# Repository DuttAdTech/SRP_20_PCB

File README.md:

### Changes Suggested by Team
- Add Debug Headers for UART Lines for GSM.
- LORA Module Footprint adjust for Hand Soldering.
- Check SRAM Compatibility - 2 MBit.
- Add Resettable Fuse after SM712 Protection Diode on MB Lines.
- Display connector change in PCB.
- PCB partision layer change (edge cut).
- Make LDO based power supply.
- SDA SCL of ADS1115 need to connected properly.
- Vbat pin of the battery measurement need to connected to the MCU.
- Add 100uF capacitor(x2) in GSM.
- Logic level shifter footprint should be SC70.
- Ground of the optocoupler and Trip should be different
- Voltage for the TFT display should be checked before doing PCB connections.

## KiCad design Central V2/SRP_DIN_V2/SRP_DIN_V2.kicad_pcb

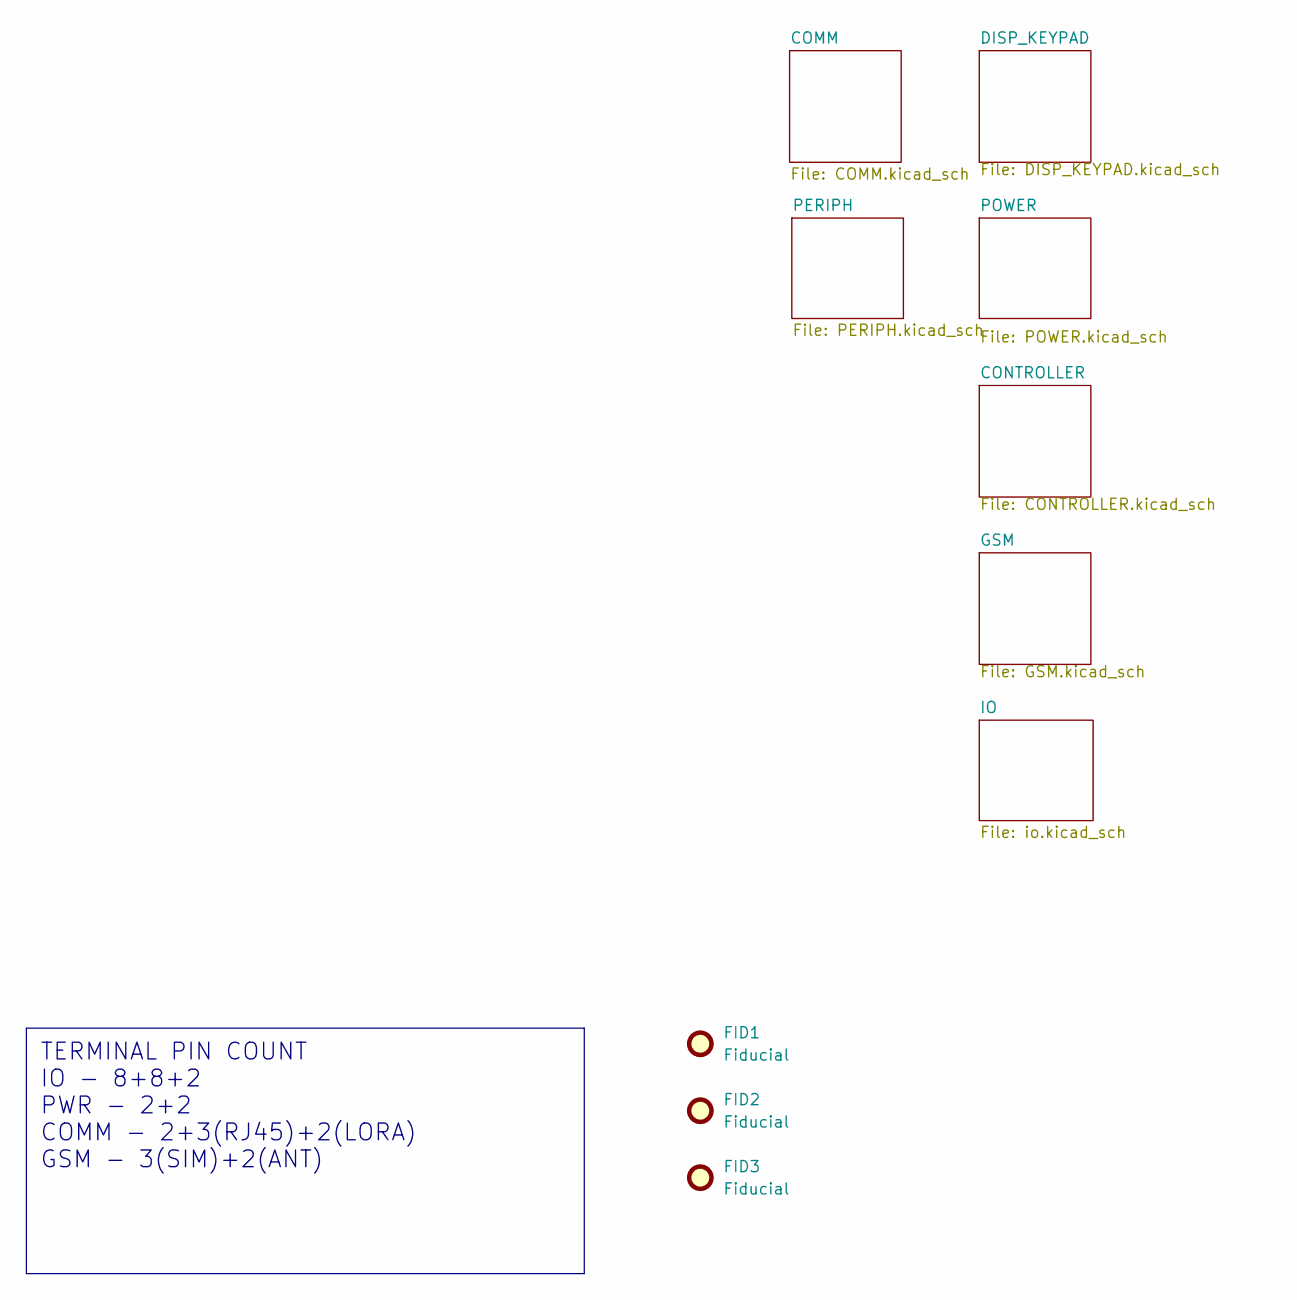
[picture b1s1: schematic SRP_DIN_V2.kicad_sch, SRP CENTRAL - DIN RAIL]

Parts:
FID1, FID2, FID3: Fiducial; Fiducial_1mm_Mask2mm

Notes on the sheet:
TERMINAL PIN COUNT IO - 8+8+2 PWR - 2+2 COMM - 2+3(RJ45)+2(LORA) GSM - 3(SIM)+2(ANT)

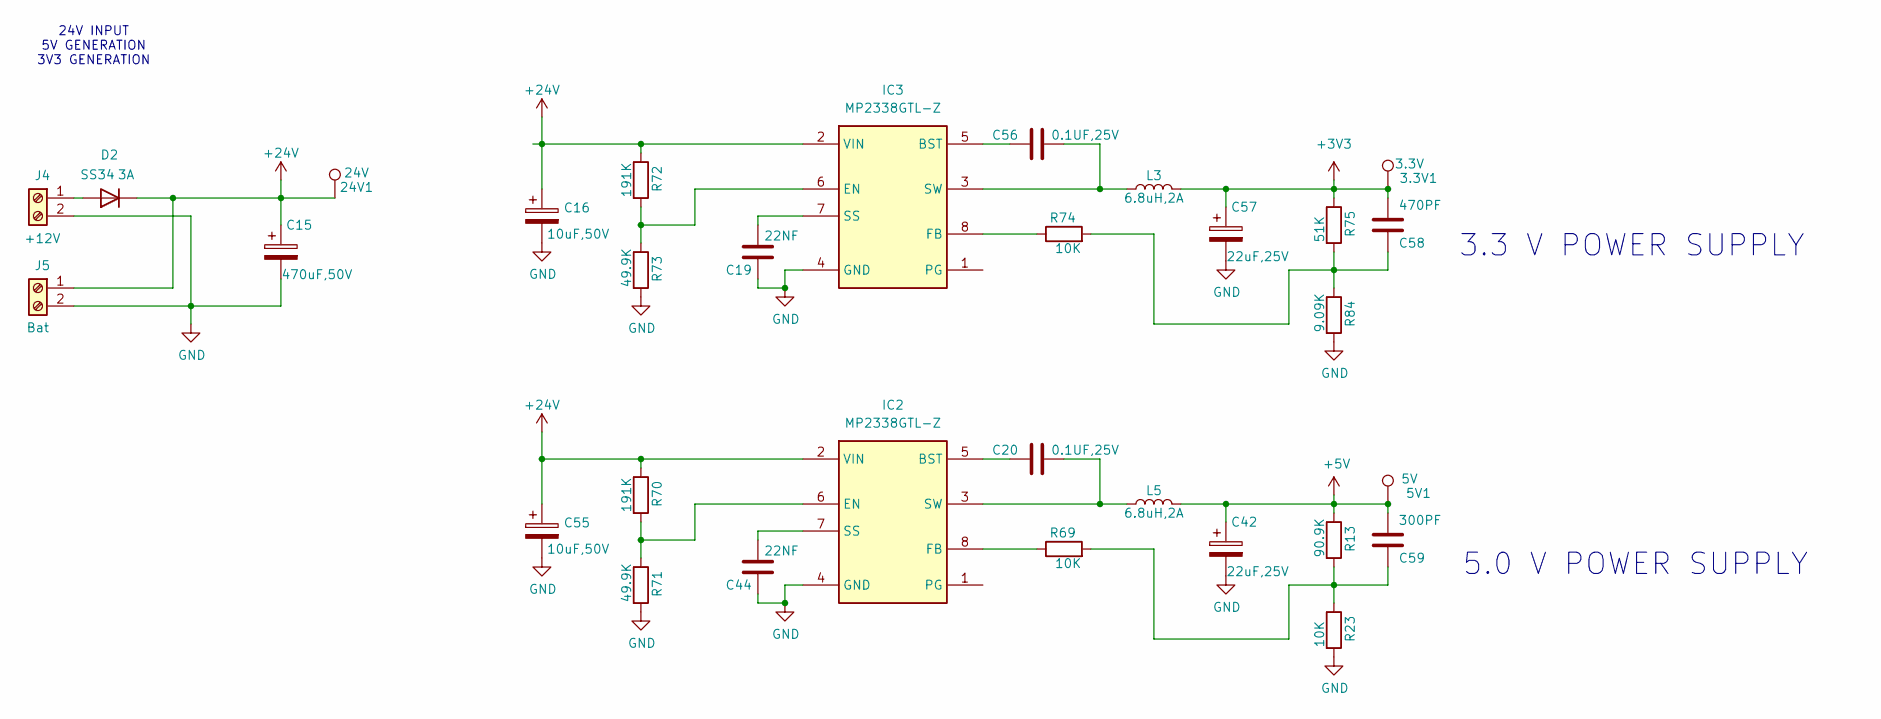
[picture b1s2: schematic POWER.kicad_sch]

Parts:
3.3V1: 3.3V; TestPoint_Pad_1.0x1.0mm
5V1: 5V; TestPoint_Pad_1.0x1.0mm
24V1: 24V; TestPoint_Pad_1.0x1.0mm
C15: 470uF,50V; CP_Elec_10x10.5
C16, C55: 10uF,50V; CP_Elec_8x5.4
C19, C44: 22NF; C_0805_2012Metric
C20, C56: 0.1UF,25V; C_0805_2012Metric
C42, C57: 22uF,25V; CP_Elec_6.3x5.3
C58: 470PF; C_0805_2012Metric
C59: 300PF; C_0805_2012Metric
D2: SS34; D_SMA
IC2, IC3: MP2338GTL-Z; SOT-583-8; Mouser Part Number 946-MP2338GTL-Z
J4: +12V; TerminalBlock_Phoenix_MKDS-3-2-5.08_1x02_P5.08mm_Horizontal
J5: Bat; TerminalBlock_Phoenix_MKDS-3-2-5.08_1x02_P5.08mm_Horizontal
L3, L5: 6.8uH,2A; L_2010_5025Metric
R13: 90.9K; R_0805_2012Metric_Pad1.20x1.40mm_HandSolder
R23, R69, R74: 10K; R_0805_2012Metric_Pad1.20x1.40mm_HandSolder
R70, R72: 191K; R_0805_2012Metric_Pad1.20x1.40mm_HandSolder
R71, R73: 49.9K; R_0805_2012Metric_Pad1.20x1.40mm_HandSolder
R75: 51K; R_0805_2012Metric_Pad1.20x1.40mm_HandSolder
R84: 9.09K; R_0805_2012Metric_Pad1.20x1.40mm_HandSolder

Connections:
+3V3: 3.3V1.1, C57.1, C58.2, L3.2, R75.1; also elsewhere on the board
+5V: 5V1.1, C42.1, C59.2, L5.2, R13.1; also elsewhere on the board
+24V: 24V1.1, C15.1, C16.1, C55.1, D2.1 (K), IC2.2 (VIN), IC3.2 (VIN), J5.1, R70.1, R72.1; also elsewhere on the board
GND: C15.2, C16.2, C19.1, C42.2, C44.1, C55.2, C57.2, IC2.4 (GND), IC3.4 (GND), J4.2, J5.2, R23.2, R71.2, R73.2, R84.2; also elsewhere on the board
unnamed: C58.1, R74.2, R75.2, R84.1
unnamed: C59.1, R13.2, R23.1, R69.2
unnamed: D2.2 (A), J4.1
unnamed: C20.1, IC2.5 (BST)
unnamed: IC2.6 (EN), R70.2, R71.1
unnamed: IC2.8 (FB), R69.1
unnamed: C44.2, IC2.7 (SS)
unnamed: C20.2, IC2.3 (SW), L5.1
unnamed: C56.1, IC3.5 (BST)
unnamed: IC3.6 (EN), R72.2, R73.1
unnamed: IC3.8 (FB), R74.1
unnamed: C19.2, IC3.7 (SS)
unnamed: C56.2, IC3.3 (SW), L3.1

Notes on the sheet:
3.3 V POWER SUPPLY
5.0 V POWER SUPPLY
24V INPUT 5V GENERATION 3V3 GENERATION

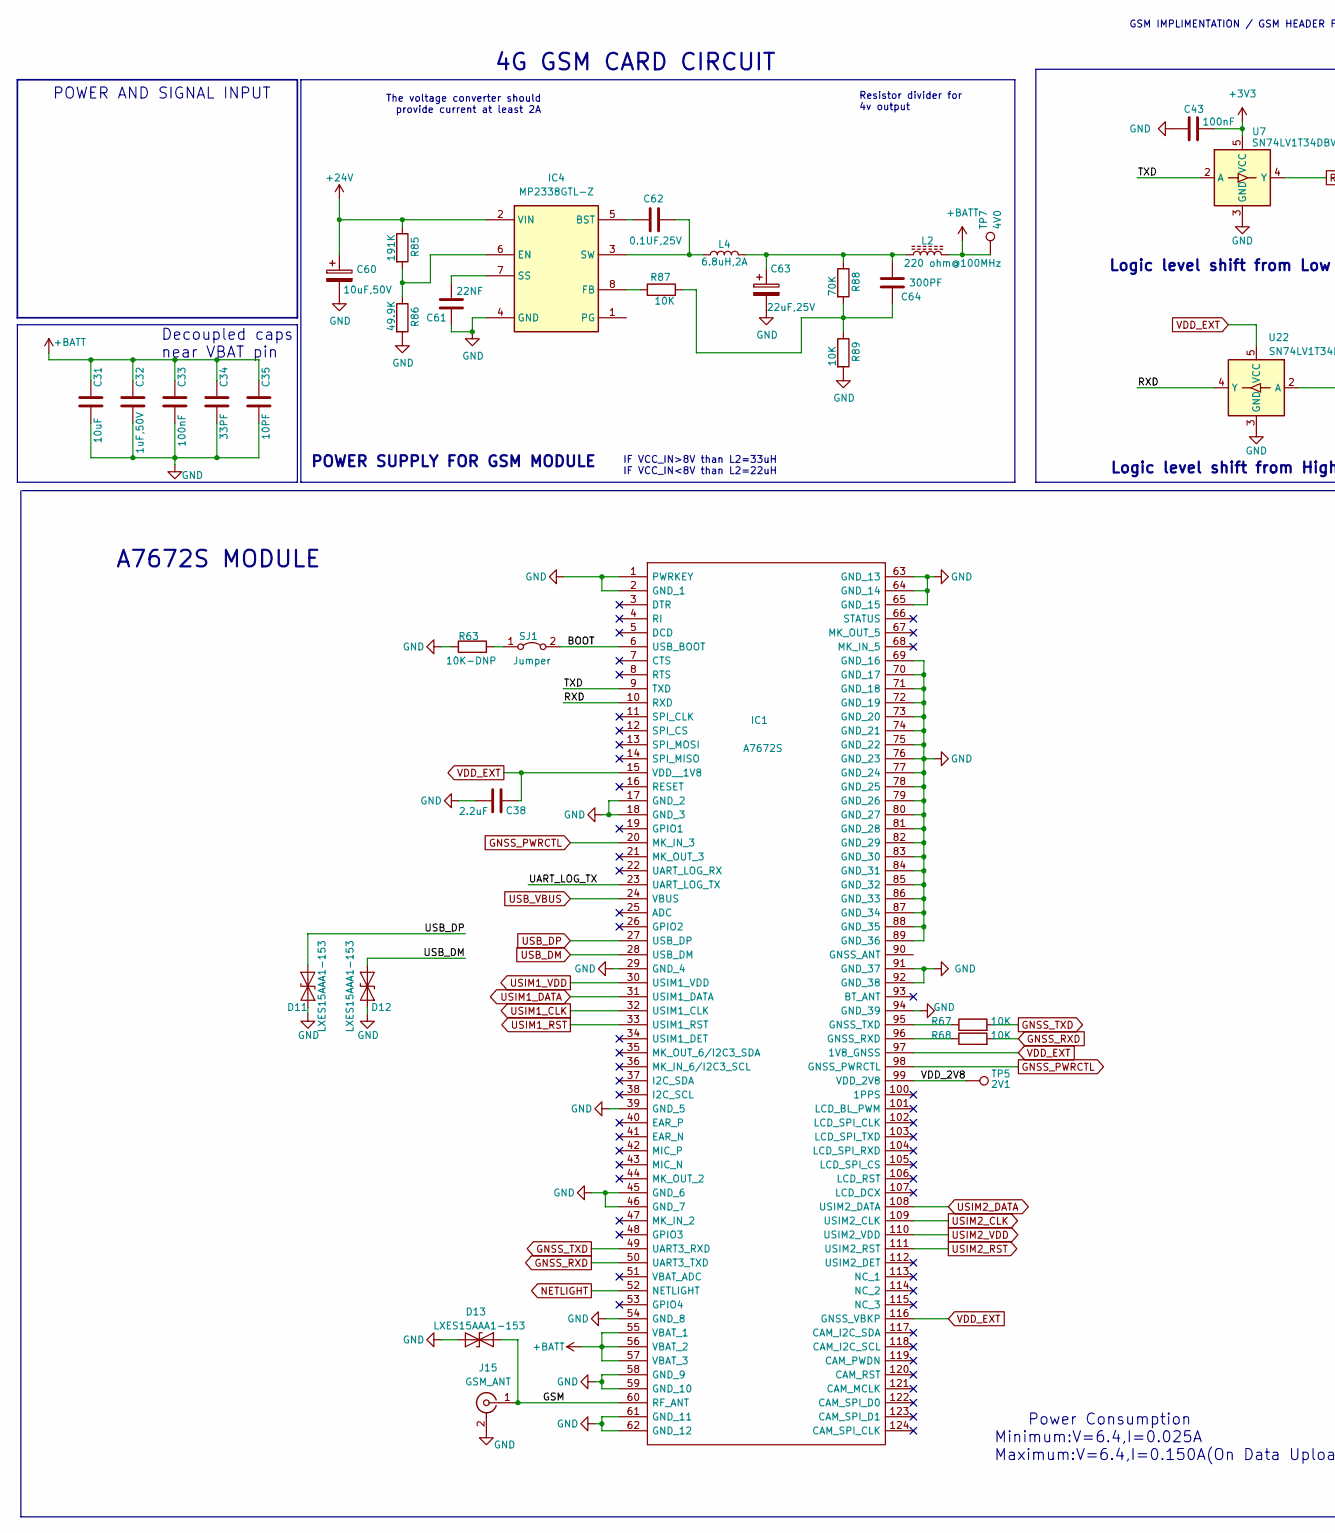
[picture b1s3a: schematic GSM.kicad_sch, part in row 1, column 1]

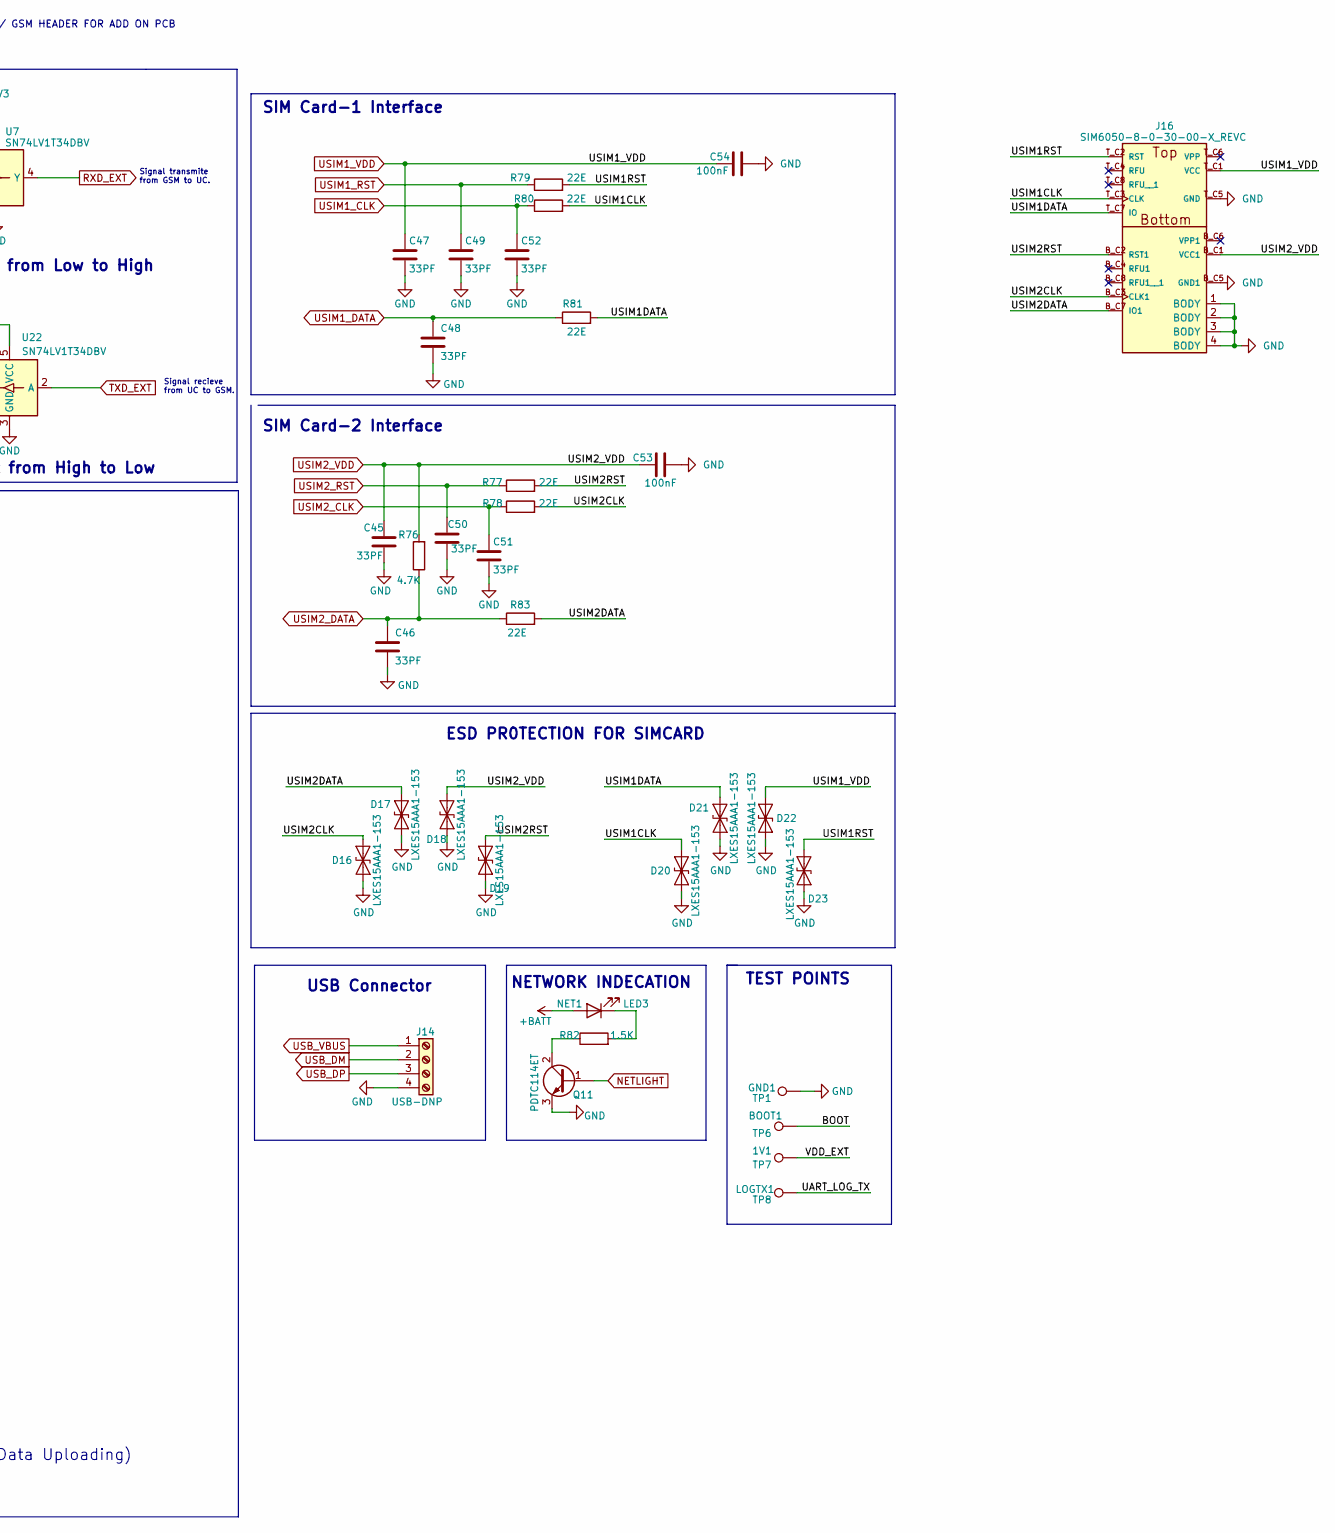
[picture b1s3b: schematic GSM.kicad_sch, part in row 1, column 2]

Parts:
1V1, 4V0: TP7; TestPoint_Pad_1.0x1.0mm
2V1: TP5; TestPoint_Pad_1.0x1.0mm
BOOT1: TP6; TestPoint_Pad_1.0x1.0mm
C31: 10uF; C_0805_2012Metric
C32: 1uF,50V; C_0805_2012Metric
C33, C43, C53, C54: 100nF; C_0805_2012Metric
C34, C45, C46, C47, C48, C49, C50, C51, C52: 33PF; C_0805_2012Metric
C35: 10PF; C_0805_2012Metric
C38: 2.2uF; C_0805_2012Metric
C60: 10uF,50V; CP_Elec_6.3x5.3
C61: 22NF; C_0805_2012Metric
C62: 0.1UF,25V; C_0805_2012Metric
C63: 22uF,25V; CP_Elec_6.3x5.3
C64: 300PF; C_0805_2012Metric
D11, D12, D13, D16, D17, D18, D19, D20, D21, D22, D23: LXES15AAA1-153; D_0402_1005Metric_Pad0.77x0.64mm_HandSolder
GND1: TP1; TestPoint_Pad_1.0x1.0mm
IC1: A7672S; A7672SA; Manufacturer_Part_Number A7672SA
IC4: MP2338GTL-Z; SOT-583-8; Mouser Part Number 946-MP2338GTL-Z
J14: USB-DNP; PinHeader_1x04_P2.54mm_Vertical
J15: GSM_ANT; SMA_Amphenol_901-144_Vertical
J16: SIM6050-8-0-30-00-X_REVC; GCT_SIM6050-8-0-30-00-X_REVC
L2: 220 ohm@100MHz; L_0805_2012Metric
L4: 6.8uH,2A; L_2010_5025Metric
LOGTX1: TP8; TestPoint_Pad_1.0x1.0mm
NET1: LED3; LED_0805_2012Metric_Pad1.15x1.40mm_HandSolder
Q11: PDTC114ET; SOT-23
R63: 10K-DNP; R_0805_2012Metric
R67, R68: 10K; R_0805_2012Metric
R76: 4.7K; R_0805_2012Metric
R77, R78, R79, R80, R81, R83: 22E; R_0805_2012Metric
R82: 1.5K; R_0805_2012Metric
R85: 191K; R_0805_2012Metric_Pad1.20x1.40mm_HandSolder
R86: 49.9K; R_0805_2012Metric_Pad1.20x1.40mm_HandSolder
R87, R89: 10K; R_0805_2012Metric_Pad1.20x1.40mm_HandSolder
R88: 70K; R_0805_2012Metric_Pad1.20x1.40mm_HandSolder
SJ1: Jumper; SolderJumper-2_P1.3mm_Open_Pad1.0x1.5mm
U7, U22: SN74LV1T34DBV; SOT-23-5

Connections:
+3V3: C43.2, U7.5 (VCC); also elsewhere on the board
+24V: C60.1, IC4.2 (VIN), R85.1; also elsewhere on the board
+BATT: 4V0.1, C31.1, C32.1, C33.1, C34.1, C35.1, IC1.55 (VBAT_1), IC1.56 (VBAT_2), IC1.57 (VBAT_3), L2.2, NET1.2 (A)
/GSM/BOOT: BOOT1.1, IC1.6 (USB_BOOT), SJ1.2 (B)
/GSM/GSM: D13.1 (A1), IC1.60 (RF_ANT), J15.1 (In)
/GSM/RXD: IC1.10 (RXD), U22.4 (Y)
/GSM/TXD: IC1.9 (TXD), U7.2 (A)
/GSM/UART_LOG_TX: IC1.23 (UART_LOG_TX), LOGTX1.1
/GSM/USIM1CLK: D20.2 (A2), J16.T_C3 (CLK), R80.2
/GSM/USIM1DATA: D21.2 (A2), J16.T_C7 (IO), R81.2
/GSM/USIM1RST: D23.2 (A2), J16.T_C2 (RST), R79.2
/GSM/USIM2CLK: D16.2 (A2), J16.B_C3 (CLK1), R78.2
/GSM/USIM2DATA: D17.2 (A2), J16.B_C7 (IO1), R83.2
/GSM/USIM2RST: D19.2 (A2), J16.B_C2 (RST1), R77.2
/GSM/VDD_2V8: 2V1.1, IC1.99 (VDD_2V8)
GND: C31.2, C32.2, C33.2, C34.2, C35.2, C38.2, C43.1, C45.2, C46.2, C47.2, C48.2, C49.2, C50.2, C51.2, C52.2, C53.2, C54.2, C60.2, C61.1, C63.2, D11.1 (A1), D12.1 (A1), D13.2 (A2), D16.1 (A1), D17.1 (A1), D18.1 (A1), D19.1 (A1), D20.1 (A1), D21.1 (A1), D22.1 (A1), D23.1 (A1), GND1.1, IC1.1 (PWRKEY), IC1.2 (GND_1), IC1.17 (GND_2), IC1.18 (GND_3), IC1.29 (GND_4), IC1.39 (GND_5), IC1.45 (GND_6), IC1.46 (GND_7), IC1.54 (GND_8), IC1.58 (GND_9), IC1.59 (GND_10), IC1.61 (GND_11), IC1.62 (GND_12), IC1.63 (GND_13), IC1.64 (GND_14), IC1.65 (GND_15), IC1.69 (GND_16), IC1.70 (GND_17), IC1.71 (GND_18), IC1.72 (GND_19), IC1.73 (GND_20), IC1.74 (GND_21), IC1.75 (GND_22), IC1.76 (GND_23), IC1.77 (GND_24), IC1.78 (GND_25), IC1.79 (GND_26), IC1.80 (GND_27), IC1.81 (GND_28), IC1.82 (GND_29), IC1.83 (GND_30), IC1.84 (GND_31), IC1.85 (GND_32), IC1.86 (GND_33), IC1.87 (GND_34), IC1.88 (GND_35), IC1.89 (GND_36), IC1.91 (GND_37), IC1.92 (GND_38), IC1.94 (GND_39), IC4.4 (GND), J14.4, J15.2 (Ext), J16.1 (BODY), J16.2 (BODY), J16.3 (BODY), J16.4 (BODY), J16.B_C5 (GND1), J16.T_C5 (GND), Q11.3 (E), R63.1, R86.2, R89.2, U7.3 (GND), U22.3 (GND); also elsewhere on the board
GNSS_PWRCTL: IC1.20 (MK_IN_3), IC1.98 (GNSS_PWRCTL)
GNSS_RXD: IC1.50 (UART3_TXD), R68.2
GNSS_TXD: IC1.49 (UART3_RXD), R67.2
NETLIGHT: IC1.52 (NETLIGHT), Q11.1 (B)
unnamed: C63.1, C64.2, L2.1, L4.2, R88.1
unnamed: C64.1, R87.2, R88.2, R89.1
unnamed: IC1.96 (GNSS_RXD), R68.1
unnamed: IC1.95 (GNSS_TXD), R67.1
unnamed: C62.1, IC4.5 (BST)
unnamed: IC4.6 (EN), R85.2, R86.1
unnamed: IC4.8 (FB), R87.1
unnamed: C61.2, IC4.7 (SS)
unnamed: C62.2, IC4.3 (SW), L4.1
unnamed: NET1.1 (K), R82.2
unnamed: Q11.2 (C), R82.1
unnamed: R63.2, SJ1.1 (A)
RXD_EXT: U7.4 (Y); also elsewhere on the board
TXD_EXT: U22.2 (A); also elsewhere on the board
USB_DM: D12.2 (A2), IC1.28 (USB_DM), J14.2
USB_DP: D11.2 (A2), IC1.27 (USB_DP), J14.3
USB_VBUS: IC1.24 (VBUS), J14.1
USIM1_CLK: C52.1, IC1.32 (USIM1_CLK), R80.1
USIM1_DATA: C48.1, IC1.31 (USIM1_DATA), R81.1
USIM1_RST: C49.1, IC1.33 (USIM1_RST), R79.1
USIM1_VDD: C47.1, C54.1, D22.2 (A2), IC1.30 (USIM1_VDD), J16.T_C1 (VCC)
USIM2_CLK: C51.1, IC1.109 (USIM2_CLK), R78.1
USIM2_DATA: C46.1, IC1.108 (USIM2_DATA), R76.1, R83.1
USIM2_RST: C50.1, IC1.111 (USIM2_RST), R77.1
USIM2_VDD: C45.1, C53.1, D18.2 (A2), IC1.110 (USIM2_VDD), J16.B_C1 (VCC1), R76.2
VDD_EXT: 1V1.1, C38.1, IC1.15 (VDD__1V8), IC1.97 (1V8_GNSS), IC1.116 (GNSS_VBKP), U22.5 (VCC)

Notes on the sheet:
NETWORK INDECATION
TEST POINTS
ESD PR0TECTION FOR SIMCARD
Logic level shift from High to Low
4G GSM CARD CIRCUIT
SIM Card-2 Interface
Signal transmite from GSM to UC.
Logic level shift from Low to High
A7672S MODULE
The voltage converter should provide current at least 2A
Resistor divider for 4v output
POWER SUPPLY FOR GSM MODULE
Signal recieve from UC to GSM.
GSM IMPLIMENTATION / GSM HEADER FOR ADD ON PCB
Power Consumption Minimum:V=6.4,I=0.025A Maximum:V=6.4,I=0.150A(On Data Uploading)
IF VCC_IN>8V than L2=33uH IF VCC_IN<8V than L2=22uH
POWER AND SIGNAL INPUT
Decoupled caps near VBAT pin
SIM Card-1 Interface
USB Connector

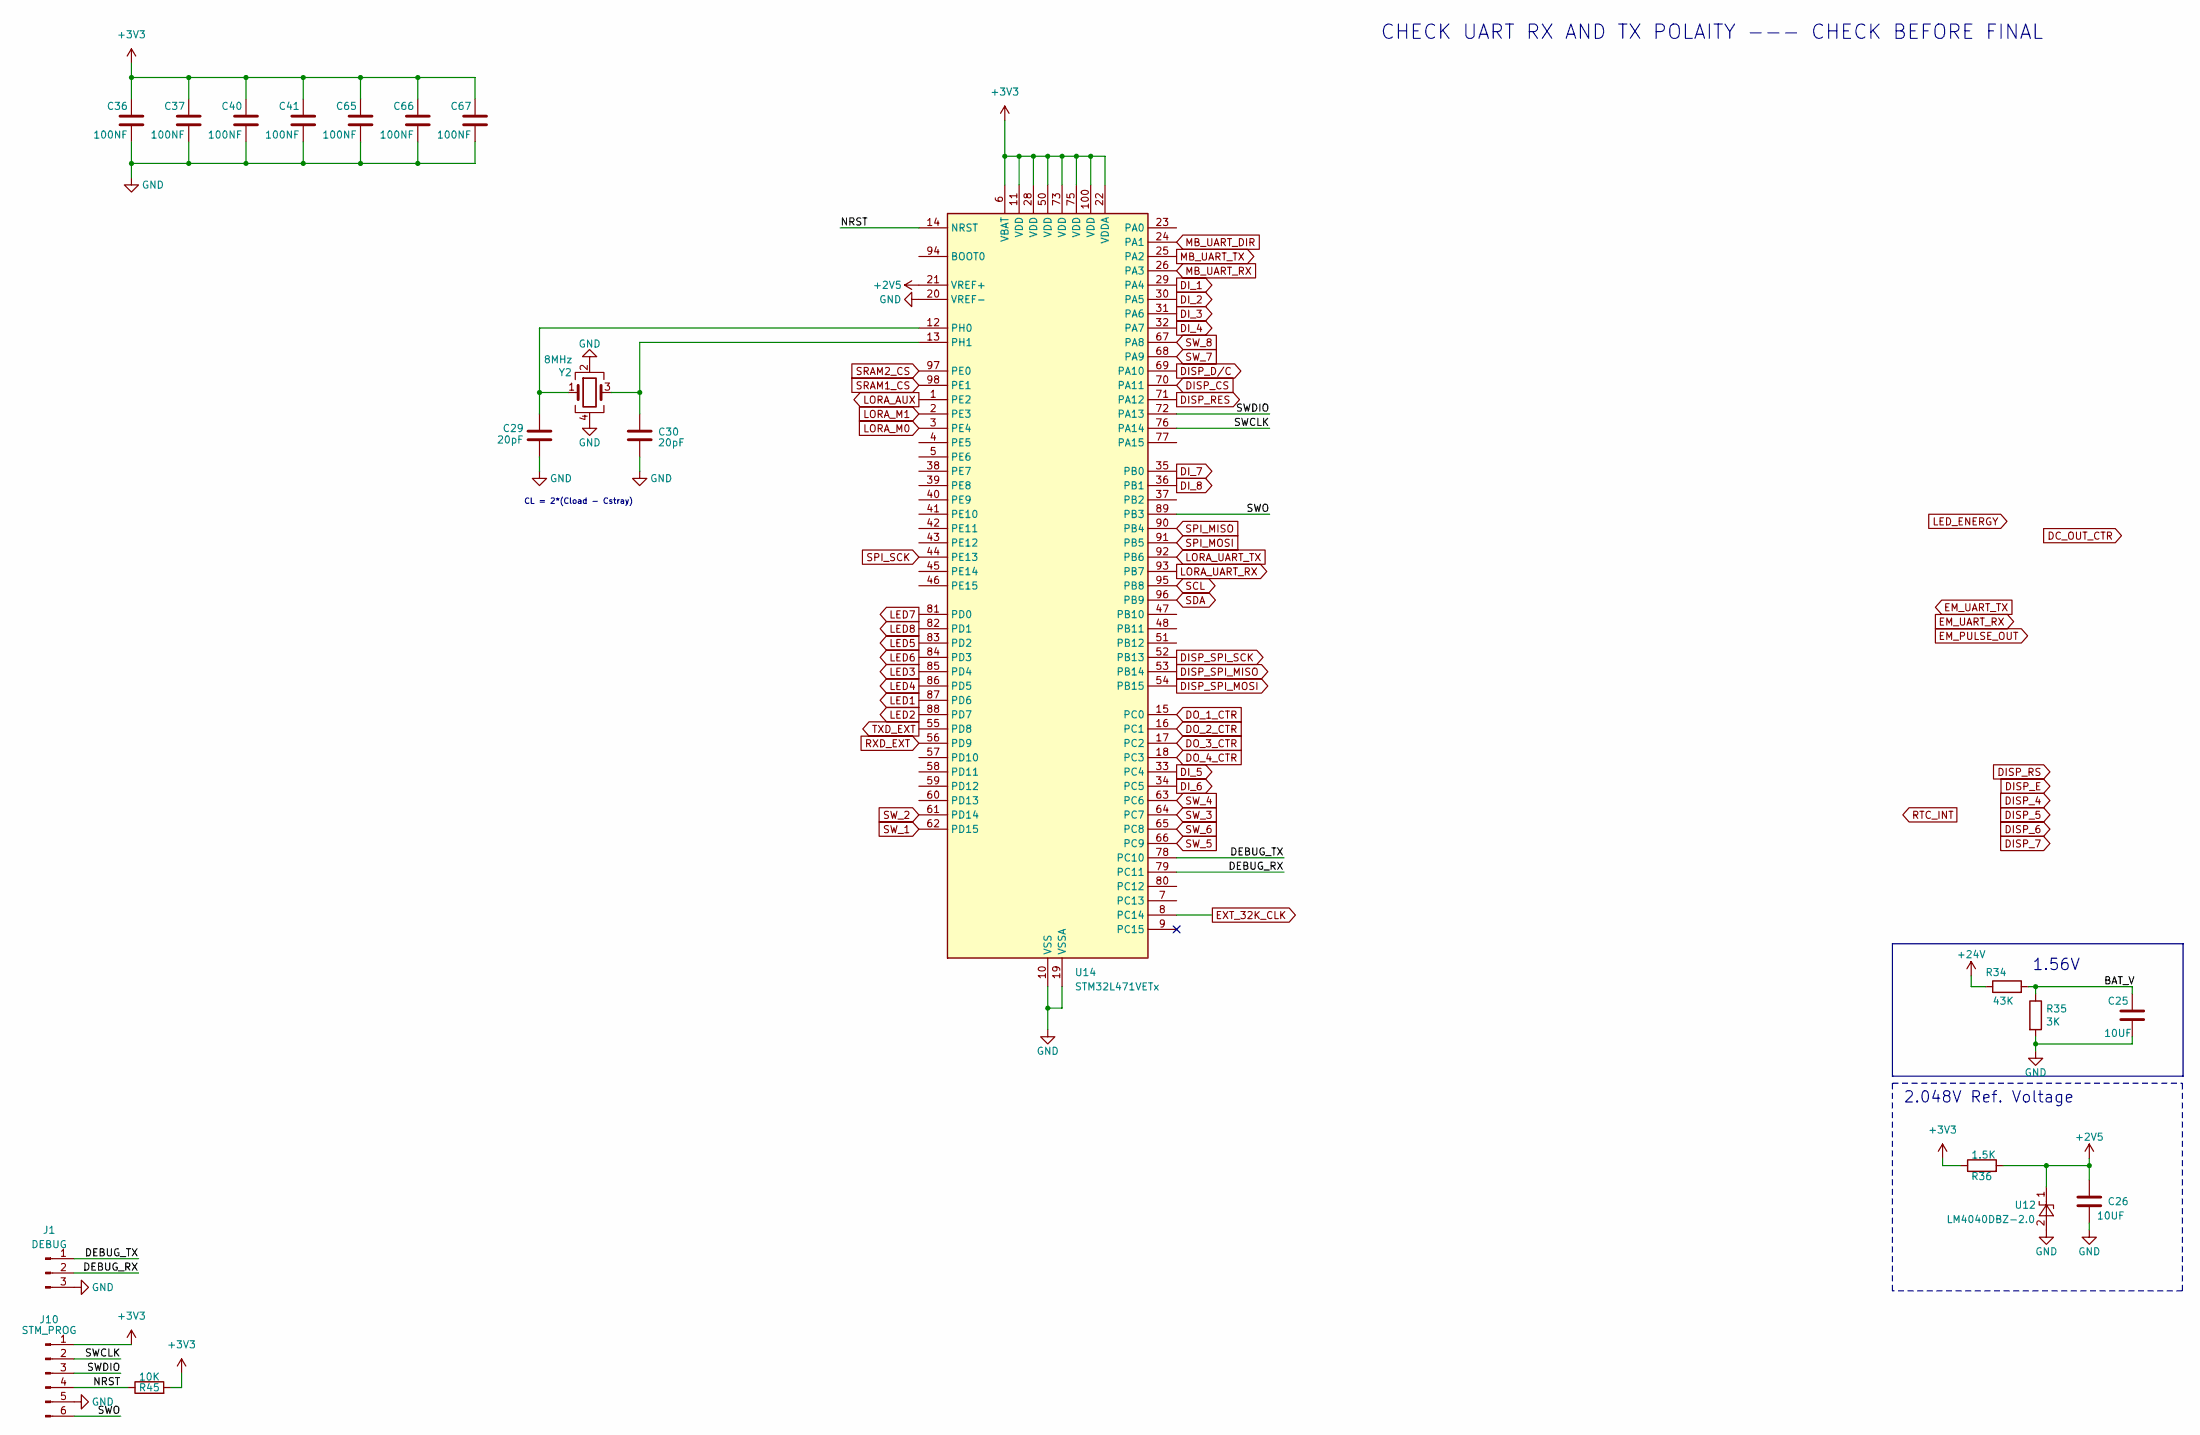
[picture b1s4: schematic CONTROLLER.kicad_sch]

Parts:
C25, C26: 10UF; C_0805_2012Metric
C29, C30: 20pF; C_0805_2012Metric
C36, C37, C40, C41, C65, C66, C67: 100NF; C_0805_2012Metric
J1: DEBUG; PinSocket_1x03_P2.54mm_Vertical
J10: STM_PROG; PinSocket_1x06_P2.54mm_Vertical
R34: 43K; R_0805_2012Metric
R35: 3K; R_0805_2012Metric
R36: 1.5K; R_0805_2012Metric
R45: 10K; R_0805_2012Metric
U12: LM4040DBZ-2.0; SOT-23
U14: STM32L471VETx; LQFP-100_14x14mm_P0.5mm
Y2: 8MHz; Crystal_SMD_Abracon_ABM3B-4Pin_5.0x3.2mm

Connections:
+2V5: C26.1, R36.2, U12.1 (K), U14.21 (VREF+)
+3V3: C36.1, C37.1, C40.1, C41.1, C65.1, C66.1, C67.1, J10.1, R36.1, R45.2, U14.6 (VBAT), U14.11 (VDD), U14.22 (VDDA), U14.28 (VDD), U14.50 (VDD), U14.73 (VDD), U14.75 (VDD), U14.100 (VDD); also elsewhere on the board
+24V: R34.1; also elsewhere on the board
/CONTROLLER/BAT_V: C25.1, R34.2, R35.1
/CONTROLLER/DEBUG_RX: J1.2, U14.79 (PC11)
/CONTROLLER/DEBUG_TX: J1.1, U14.78 (PC10)
/CONTROLLER/NRST: J10.4, R45.1, U14.14 (NRST)
/CONTROLLER/SWCLK: J10.2, U14.76 (PA14)
/CONTROLLER/SWDIO: J10.3, U14.72 (PA13)
/CONTROLLER/SWO: J10.6, U14.89 (PB3)
DISP_CS: U14.70 (PA11); also elsewhere on the board
DISP_D/C: U14.69 (PA10); also elsewhere on the board
DISP_RES: U14.71 (PA12); also elsewhere on the board
DISP_SPI_MISO: U14.53 (PB14)
DISP_SPI_MOSI: U14.54 (PB15); also elsewhere on the board
DISP_SPI_SCK: U14.52 (PB13); also elsewhere on the board
DI_1: U14.29 (PA4); also elsewhere on the board
DI_2: U14.30 (PA5); also elsewhere on the board
DI_3: U14.31 (PA6); also elsewhere on the board
DI_4: U14.32 (PA7); also elsewhere on the board
DI_5: U14.33 (PC4); also elsewhere on the board
DI_6: U14.34 (PC5); also elsewhere on the board
DI_7: U14.35 (PB0); also elsewhere on the board
DI_8: U14.36 (PB1); also elsewhere on the board
DO_1_CTR: U14.15 (PC0); also elsewhere on the board
DO_2_CTR: U14.16 (PC1); also elsewhere on the board
DO_3_CTR: U14.17 (PC2); also elsewhere on the board
DO_4_CTR: U14.18 (PC3); also elsewhere on the board
EXT_32K_CLK: U14.8 (PC14); also elsewhere on the board
GND: C25.2, C26.2, C29.2, C30.2, C36.2, C37.2, C40.2, C41.2, C65.2, C66.2, C67.2, J1.3, J10.5, R35.2, U12.2 (A), U14.10 (VSS), U14.19 (VSSA), U14.20 (VREF-), U14.27 (VSS), U14.49 (VSS), U14.74 (VSS), U14.99 (VSS), Y2.2, Y2.4; also elsewhere on the board
LED1: U14.87 (PD6); also elsewhere on the board
LED2: U14.88 (PD7); also elsewhere on the board
LED3: U14.85 (PD4); also elsewhere on the board
LED4: U14.86 (PD5); also elsewhere on the board
LED5: U14.83 (PD2); also elsewhere on the board
LED6: U14.84 (PD3); also elsewhere on the board
LED7: U14.81 (PD0); also elsewhere on the board
LED8: U14.82 (PD1); also elsewhere on the board
LORA_AUX: U14.1 (PE2); also elsewhere on the board
LORA_M0: U14.3 (PE4); also elsewhere on the board
LORA_M1: U14.2 (PE3); also elsewhere on the board
LORA_UART_RX: U14.93 (PB7); also elsewhere on the board
LORA_UART_TX: U14.92 (PB6); also elsewhere on the board
MB_UART_DIR: U14.24 (PA1); also elsewhere on the board
MB_UART_RX: U14.26 (PA3); also elsewhere on the board
MB_UART_TX: U14.25 (PA2); also elsewhere on the board
unnamed: C29.1, U14.12 (PH0), Y2.1
unnamed: C30.1, U14.13 (PH1), Y2.3
RXD_EXT: U14.56 (PD9); also elsewhere on the board
SCL: U14.95 (PB8); also elsewhere on the board
SDA: U14.96 (PB9); also elsewhere on the board
SPI_MISO: U14.90 (PB4); also elsewhere on the board
SPI_MOSI: U14.91 (PB5); also elsewhere on the board
SPI_SCK: U14.44 (PE13); also elsewhere on the board
SRAM1_CS: U14.98 (PE1); also elsewhere on the board
SRAM2_CS: U14.97 (PE0); also elsewhere on the board
SW_1: U14.62 (PD15); also elsewhere on the board
SW_2: U14.61 (PD14); also elsewhere on the board
SW_3: U14.64 (PC7); also elsewhere on the board
SW_4: U14.63 (PC6); also elsewhere on the board
SW_5: U14.66 (PC9); also elsewhere on the board
SW_6: U14.65 (PC8); also elsewhere on the board
SW_7: U14.68 (PA9); also elsewhere on the board
SW_8: U14.67 (PA8); also elsewhere on the board
TXD_EXT: U14.55 (PD8); also elsewhere on the board

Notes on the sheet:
CHECK UART RX AND TX POLAITY --- CHECK BEFORE FINAL
CL = 2*(Cload - Cstray)
2.048V Ref. Voltage
1.56V

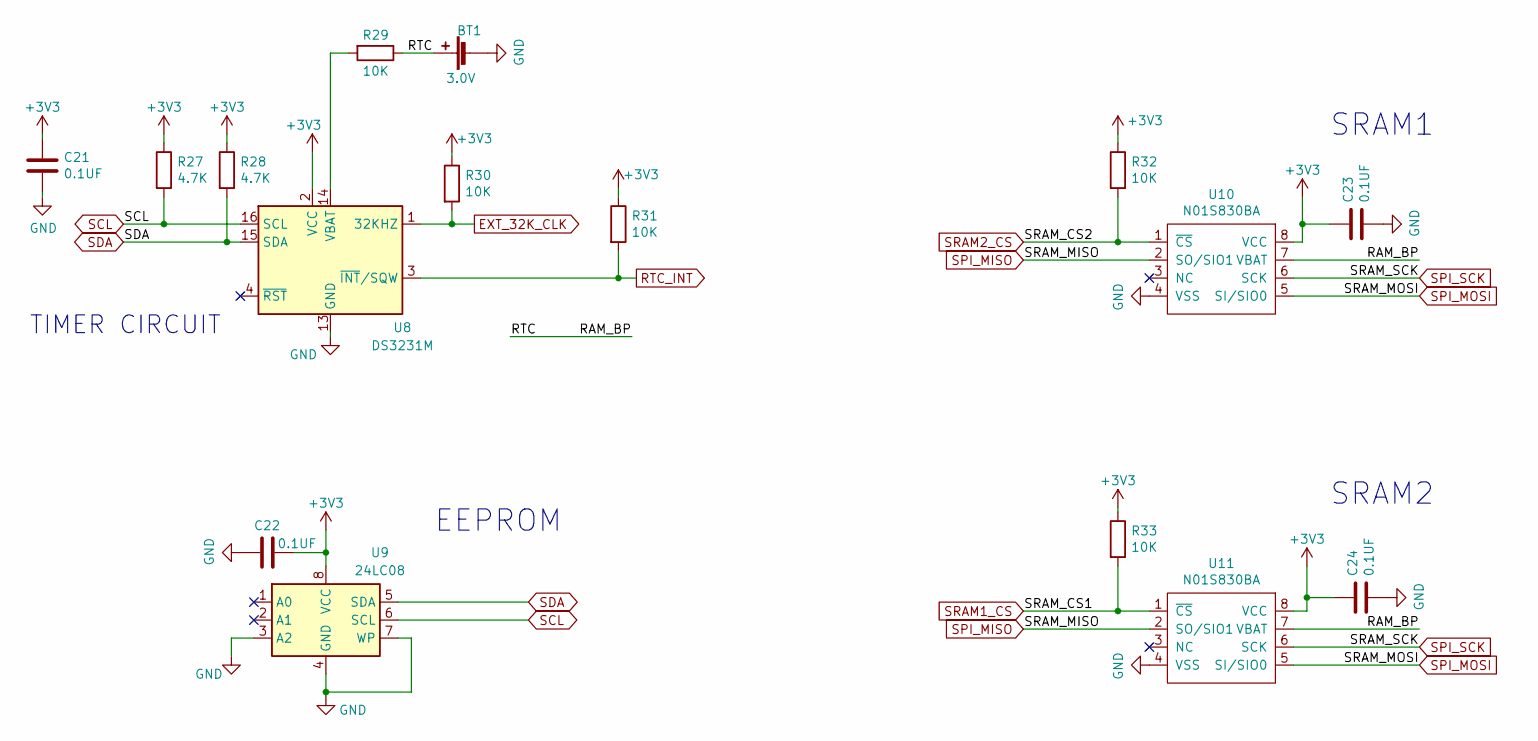
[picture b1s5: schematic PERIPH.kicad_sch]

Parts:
BT1: 3.0V; RTC_2032_VERTICLE_HOLDER
C21, C22, C23, C24: 0.1UF; C_0805_2012Metric
R27, R28: 4.7K; R_0805_2012Metric
R29, R30, R31, R32, R33: 10K; R_0805_2012Metric
U8: DS3231M; SOIC-16W_7.5x10.3mm_P1.27mm
U9: 24LC08; SOIC-8_3.9x4.9mm_P1.27mm
U10, U11: N01S830BA; TSSOP-8_4.4x3mm_P0.65mm

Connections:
+3V3: C21.1, C22.2, C23.1, C24.1, R27.1, R28.1, R30.1, R31.1, R32.1, R33.1, U8.2 (VCC), U9.8 (VCC), U10.8 (VCC), U11.8 (VCC); also elsewhere on the board
/PERIPH/RAM_BP: BT1.1 (+), R29.1, U10.7 (VBAT), U11.7 (VBAT)
EXT_32K_CLK: R30.2, U8.1 (32KHZ); also elsewhere on the board
GND: BT1.2 (-), C21.2, C22.1, C23.2, C24.2, U8.5 (GND), U8.6 (GND), U8.7 (GND), U8.8 (GND), U8.9 (GND), U8.10 (GND), U8.11 (GND), U8.12 (GND), U8.13 (GND), U9.3 (A2), U9.4 (GND), U9.7 (WP), U10.4 (VSS), U11.4 (VSS); also elsewhere on the board
unnamed: R29.2, U8.14 (VBAT)
RTC_INT: R31.2, U8.3 (~INT/SQW)
SCL: R27.2, U8.16 (SCL), U9.6 (SCL); also elsewhere on the board
SDA: R28.2, U8.15 (SDA), U9.5 (SDA); also elsewhere on the board
SPI_MISO: U10.2 (SO/SIO1), U11.2 (SO/SIO1); also elsewhere on the board
SPI_MOSI: U10.5 (SI/SIO0), U11.5 (SI/SIO0); also elsewhere on the board
SPI_SCK: U10.6 (SCK), U11.6 (SCK); also elsewhere on the board
SRAM1_CS: R33.2, U11.1 (~CS); also elsewhere on the board
SRAM2_CS: R32.2, U10.1 (~CS); also elsewhere on the board

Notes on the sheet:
SRAM1
SRAM2
TIMER CIRCUIT
EEPROM

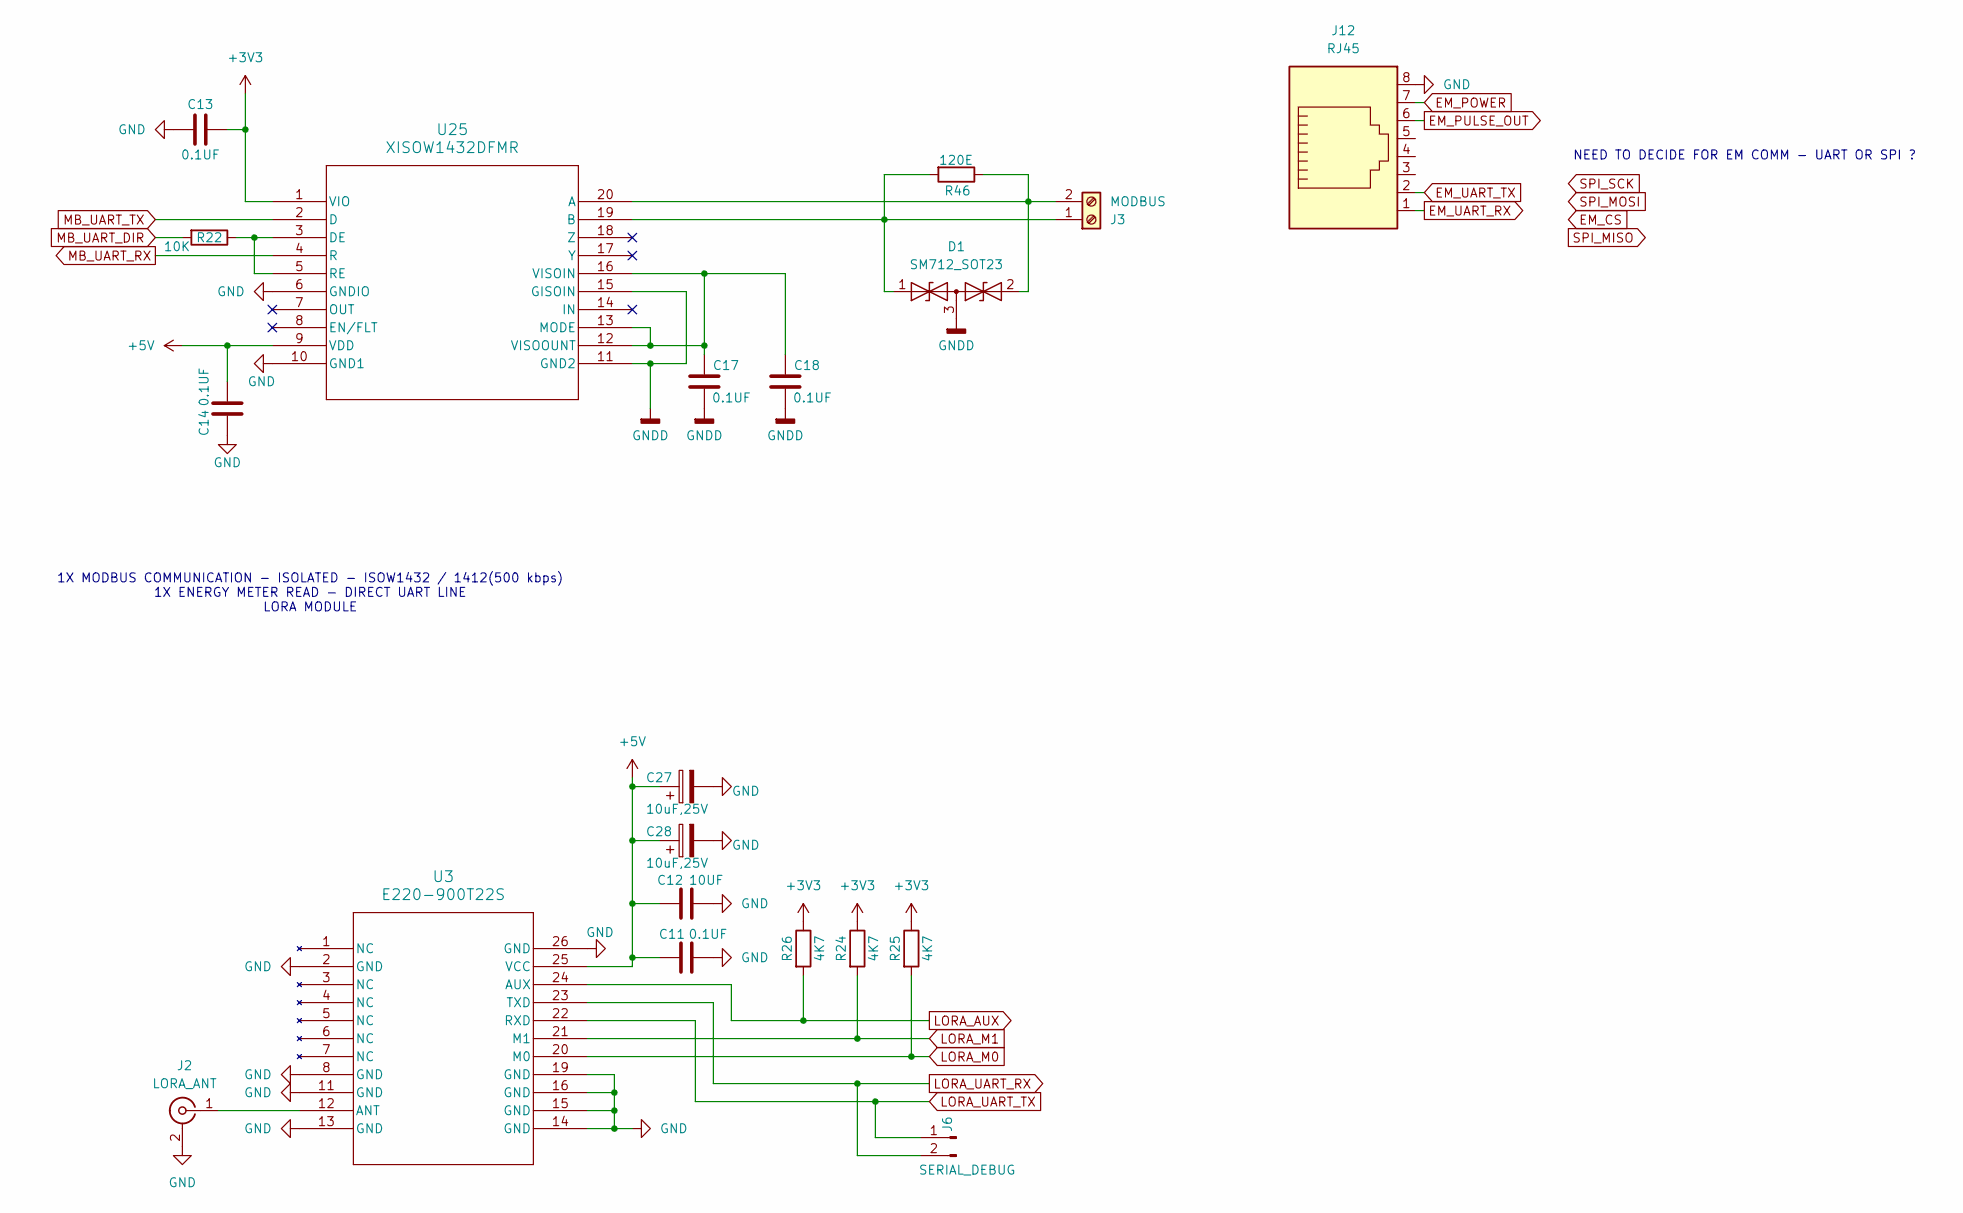
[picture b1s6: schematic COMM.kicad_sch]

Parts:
C11, C13, C14, C17, C18: 0.1UF; C_0805_2012Metric
C12: 10UF; C_0805_2012Metric
C27, C28: 10uF,25V; CP_Elec_4x5.4
D1: SM712_SOT23; SOT-23
J2: LORA_ANT; SMA_Amphenol_901-144_Vertical
J3: MODBUS; TerminalBlock_Phoenix_MKDS-3-2-5.08_1x02_P5.08mm_Horizontal
J6: SERIAL_DEBUG; PinSocket_1x02_P2.54mm_Vertical
J12: RJ45; RJ45_Amphenol_54602-x08_Horizontal
R22: 10K; R_0805_2012Metric
R24, R25, R26: 4K7; R_0805_2012Metric
R46: 120E; R_0805_2012Metric_Pad1.20x1.40mm_HandSolder
U3: E220-900T22S
U25: XISOW1432DFMR; U_ISOW1432_TEX

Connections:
+3V3: C13.1, R24.1, R25.1, R26.1, U25.1 (VIO); also elsewhere on the board
+5V: C11.1, C12.1, C14.2, C27.1, C28.1, U3.25 (VCC), U25.9 (VDD); also elsewhere on the board
EM_POWER: J12.7
EM_PULSE_OUT: J12.6
EM_UART_RX: J12.1
EM_UART_TX: J12.2
GND: C11.2, C12.2, C13.2, C14.1, C27.2, C28.2, J2.2 (Ext), J12.8, U3.2 (GND), U3.8 (GND), U3.11 (GND), U3.13 (GND), U3.14 (GND), U3.15 (GND), U3.16 (GND), U3.19 (GND), U3.26 (GND), U25.6 (GNDIO), U25.10 (GND1); also elsewhere on the board
GNDD: C17.1, C18.1, D1.3 (common), U25.11 (GND2), U25.15 (GISOIN)
LORA_AUX: R26.2, U3.24 (AUX); also elsewhere on the board
LORA_M0: R25.2, U3.20 (M0); also elsewhere on the board
LORA_M1: R24.2, U3.21 (M1); also elsewhere on the board
LORA_UART_RX: J6.2, U3.23 (TXD); also elsewhere on the board
LORA_UART_TX: J6.1, U3.22 (RXD); also elsewhere on the board
MB_UART_DIR: R22.2; also elsewhere on the board
MB_UART_RX: U25.4 (R); also elsewhere on the board
MB_UART_TX: U25.2 (D); also elsewhere on the board
unnamed: D1.1 (A1), J3.1, R46.2, U25.19 (B)
unnamed: D1.2 (A2), J3.2, R46.1, U25.20 (A)
unnamed: J2.1 (In), U3.12 (ANT)
unnamed: R22.1, U25.3 (DE), U25.5 (RE)
unnamed: C17.2, C18.2, U25.12 (VISOOUNT), U25.13 (MODE), U25.16 (VISOIN)

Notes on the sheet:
1X MODBUS COMMUNICATION - ISOLATED - ISOW1432 / 1412(500 kbps) 1X ENERGY METER READ - DIRECT UART LINE LORA MODULE
NEED TO DECIDE FOR EM COMM - UART OR SPI ?
